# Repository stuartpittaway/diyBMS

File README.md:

# diyBMS
Do it yourself battery management system to Lithium ion battery packs/cells

More discussion
https://community.openenergymonitor.org/t/diy-lithium-battery-balancer-and-monitoring-bms/5594/10

** PLEASE NOTE THIS DESIGN HAS BEEN REPLACED WITH VERSION 4 **

https://github.com/stuartpittaway/diyBMSv4

# YouTube

https://www.youtube.com/watch?v=-CusvENqC4I&t=12s

Some Youtube videos on the BMS building and testing can be found at
https://www.youtube.com/playlist?list=PLiYbY8lzAN-2qB9rR0Sc7Z7sUrsgYzsiV

# Problem

A DIY Powerwall is the DIY construction of a pack of battery cells to create an energy store which can be used via inverters to power electrical items in the home. Generally cells are salvaged/second hand, and typically use Lithium 18650 cells.

Lithium batteries need to be kept at the same voltage level across a parallel pack. This is done by balancing each cell in the pack to raise or lower its voltage to match the others.

Existing balancing solutions are available in the market place, but at a relatively high cost compared to the cost of the battery bank, so this project is to design a low-cost, simple featured BMS/balancer.

A large number of people have utilised the commercial BATRIUM BMS system in their powerwall devices.

# My Situtation/Environment

UK based, but with only a small setup.  I have a 7s96p setup which i need to keep in balance.

# Existing Energy Usage

Through the monitoring of my home electric usage using the emonTX and emonSD solutions I typically use around 9kW/H per day (excluding electric car charging). Apart from odd spikes, load it generally less than 500W for the majority of the day/night.

# The Plan

Install a DIY powerwall with the ability to supply a 1000W load to cover all regular home usage (excluding spikes which the grid will handle).

A grid tied inverter would be required to convert the battery DC into mains level AC.

A controllable charger would be required to charge the battery during the day (or at cheap energy times from the grid). Ideally the charger should be able to match the generation of export from the solar array(s) to prevent import.

It may be possible to combine both charger and inverter into a single unit (so called hybrid units)

For obvious reasons, safety is critical, so care must be taken to ensure components are installed and certified as needed, along with the correct specification for cables, breakers and fuses etc.

Why am I doing this? For fun :slight_smile: I really must get out more!

# WARNING

Just a reminder that this is a DIY product/solution so don’t use this for safety critical systems or in any situation where there could be a risk to life.  There is no warranty, it may not work as expected or at all.

# Parameters

I’m working to the the following design parameters, which are taken from research into the area (what most others are doing!)

Assumption that second hand 18650 cells are made into “packs” containing tens or hundreds of cells in parallel.
Voltage of 18650 cell between 3.0V (empty) and 4.2V (full)
48V DC battery pack - running 14 packs/cells in series (aka 14S) this gives between 42V and 58.8V DC
Battery expected to output (1000W) so produce up to 25A current (depending on battery voltage)
Charger and inverter would be commercial products (not DIY) to comply with necessary approvals

# BMS Design

Building upon my existing skill set and knowledge, and also building something that others can contribute to using regular standard libraries and off the shelf components.

* Design a hub and spoke arrangement, for a central controller and individual cell monitoring nodes on each pack (so 14 in my case)
* Use Arduino based libraries and tools (possible move to platform.io) **
* Use esp8266-12e as the controller - to take advantage of built in WIFI for monitoring/alerting and CPU/RAM performance
* Use AVR ATTINY85 for each node
* Ensure each cell voltage is isolated from other cells and that ground voltage is isolated
* Isolated communications between controller and node is needed
* Put everything on GITHUB
* Document it!

** There are better more capable CPUs than the 8-bit Arduino however they lack user friendliness and the community to support and nuture the development of code

# Bill Of Materials

NOTE SIZES OF COMPNENTS SHOULD BE 0805 SIZED FOR THE SMALLER PCB VARIANT!

See BMS_Cell_Module_BOM.html for details

Links to main components
ATTINY85V-10SU
http://uk.farnell.com/atmel/attiny85v-10su/mcu-8bit-attiny-10mhz-soic-8/dp/1455166

REG710NA-3.3
http://uk.farnell.com/texas-instruments/reg710na-3-3-250/charge-pump-regulator-buck-boost/dp/1535743

Analog Devices ADUM1250ARZ
http://uk.farnell.com/analog-devices/adum1250arz-rl7/digital-isolator-4-ch-1mbps-nsoic/dp/2758723

SI2312BDS-T1-E3 MOSFET Transistor, N Channel, 3.9 A, 20 V, 0.025 ohm, 4.5 V, 850 mV
http://uk.farnell.com/vishay/si2312bds-t1-e3/mosfet-n-ch-20v-3-9a-sot-23-3/dp/2396085

B57891M0103K000 Thermistor, NTC, 10 kohm, B57891M Series, 3950 K, Through Hole
http://uk.farnell.com/epcos/b57891m0103k000/thermistor-ntc-radial-leaded/dp/2285471?ost=B57891M0103K000&iscrfnonsku=false&ddkey=http%3Aen-GB%2FElement14_United_Kingdom%2Fsearch

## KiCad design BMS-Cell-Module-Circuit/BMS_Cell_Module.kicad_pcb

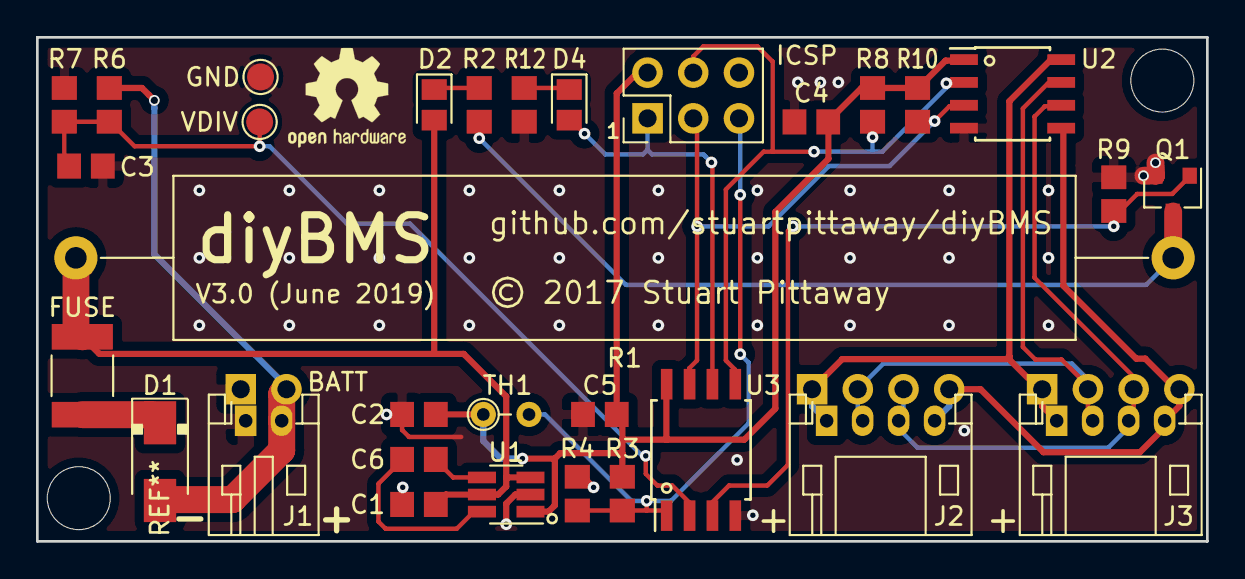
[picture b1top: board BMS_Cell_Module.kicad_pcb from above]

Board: 2 copper layers, 65.0 x 28.0 mm, 31 parts (0 on the bottom side), 20 nets.

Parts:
C1, C2: 2.2uF; C_0805_2012Metric_Pad1.33x1.40mm_HandSolder
C3, C4, C5: 0.1uF; C_0805_2012Metric_Pad1.33x1.40mm_HandSolder
C6: 0.22uF; C_0805_2012Metric_Pad1.33x1.40mm_HandSolder
D1: SS34 Schottky 40V/3A; DO-221AC
D2: LED BLUE; LED_0805_2012Metric_Pad1.15x1.40mm_HandSolder
D4: LED GREEN; LED_0805_2012Metric_Pad1.15x1.40mm_HandSolder
F1: FUSE; R_1812_4532Metric_Pad1.42x3.40mm_HandSolder
ISP1: Conn_02x03_Odd_Even; Pin_Header_Straight_2x03_Pitch2.54mm
J1: Conn_01x02_Female; JST_PH_S2B-PH-K_02x2.00mm_Angled
J2, J3: Conn_01x04_Female; JST_PH_S4B-PH-K_04x2.00mm_Angled
Q1: SI2312BDS-T1-E3; SOT-23
R1: 2R/10W; R_Axial_Power_L50.0mm_W9.0mm_P60.96mm
R2, R8, R10, R12: 4K7; R_0805_2012Metric_Pad1.33x1.40mm_HandSolder
R3: 20K; R_0805_2012Metric_Pad1.33x1.40mm_HandSolder
R4: 10K; R_0805_2012Metric_Pad1.33x1.40mm_HandSolder
R6: 510K; R_0805_2012Metric_Pad1.33x1.40mm_HandSolder
R7: 680K; R_0805_2012Metric_Pad1.33x1.40mm_HandSolder
R9: 47K; R_0805_2012Metric_Pad1.33x1.40mm_HandSolder
TH1: B57891M0103K000; R_Axial_DIN0204_L3.6mm_D1.6mm_P2.54mm_Vertical
TP1: VDIV; TestPoint_Pad_D1.5mm
TP2: TPGND; TestPoint_Pad_D1.5mm
U1: REG710NA-3.3; SOT-23-6_Handsoldering
U2: ADUM1250ARZ; SOIC-8_3.9x4.9mm_P1.27mm
U3: ATTINY85V-10SU 8S2 EIAJ SOIC; SOIJ-8_5.3x5.3mm_P1.27mm

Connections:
3V3: C2.1, C4.1, C5.1, ISP1.2, R3.1, R8.2, R10.2, TH1.1, U1.1, U2.1, U3.8
/MISO: D4.2, ISP1.1, U3.6
/MOSI: ISP1.4, R8.1, U2.2, U3.5
/PB4BYPASS: Q1.1, R9.1, U3.3
/RST: ISP1.5, R3.2, R4.1, TH1.2, U3.1
/SCK: ISP1.3, R10.1, U2.3, U3.7
BATT+RAW: D1.2, J1.2, R6.1
GND: C1.2, C2.2, C3.2, C4.2, C5.2, ISP1.6, J1.1, Q1.2, R4.2, R7.2, R9.2, R12.2, TP2.1, U1.2, U2.4, U3.4
unnamed: C1.1, D2.2, F1.1, R1.2, U1.3, U1.5
unnamed: C3.1, R6.2, R7.1, TP1.1, U3.2
unnamed: C6.1, U1.6
unnamed: C6.2, U1.4
unnamed: D1.1, F1.2
unnamed: D2.1, R2.2
unnamed: D4.1, R12.1
unnamed: J2.1, J3.1, U2.8
unnamed: J2.2, J3.2, U2.7
unnamed: J2.3, J3.3, U2.6
unnamed: J2.4, J3.4, U2.5
unnamed: Q1.3, R1.1, R2.1

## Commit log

2017-11-09 Initial cell monitoring circuit
2017-11-09 Started work on PCB
    DONT USE THIS PCB FOR PRODUCTION!
2017-11-12 Split board into two sections
2017-11-13 Split PCB into two halves
2017-11-13 All pins connected on PCB
2017-11-13 PCB files
2017-11-14 Update fuse and power socket
2017-11-14 Added ground plane to pcb
2017-11-14 First Gerber files
2017-11-14 Remove obsolete files
2017-11-14 Remove files
2017-11-16 Updated gerbers with bottom solder mask
2017-11-16 Project file changes
2017-11-17 Beta code in development
2017-11-17 Added header text
2017-11-18 Getting i2c to work properly
2017-11-19 Debugging ESP8266 crappy i2c issues
    Clock stretching appears to be breaking ESP8266 code
2017-11-20 Working i2c using wire library
2017-11-20 Changed freq to 8Mhz to improve i2c handling
2017-11-20 Delay after changing MUX in ADC ISR
2017-11-22 Write configuration to EEPROM and trigger LED on TIMER1
2017-11-22 Code tidy
2017-11-23 Implemented watchdog timeout and factory reset functions
2017-11-23 Commands to retrieve calibration values
2017-11-25 Added set calibration values functions
2017-11-26 Removed RED led and improved test functions in temporary controller
2017-11-26 Remove red led code
2017-11-27 Changed default values
2017-11-27 Test controller instructions and auto cell module provisioning
2017-11-27 Fixed error/panic mode
2017-11-27 Initial code for resistor bypass/balancing
2017-11-29 Started redesign of PCB
2017-12-02 Start of new PCB layout for v2
2017-12-02 Custom PCB footprints
2017-12-02 Updated PCB layout
2017-12-03 Revised PCB
2017-12-03 New Gerbers
2017-12-03 Update BOM
2017-12-03 Update pictures
2017-12-08 Remove backup files
2017-12-08 Tidy up test controller code
2017-12-08 Start of real DIY BMS controller
2017-12-10 Wifi AP configuration and setup
2017-12-11 Changed EEPROM update and write
2017-12-11 Split into seperate files
2017-12-11 Split code into seperate files
2017-12-11 Fixed CRC32 code not use the library!
2017-12-12 Post data into emoncms for cell module voltages and temperatures
2017-12-14 Submit Docs
2017-12-14 Set theme jekyll-theme-tactile
2017-12-14 HTML pages
2017-12-14 Added code to get IP address
2017-12-14 Graph to display
2018-01-06 Minor tweaks
2018-01-06 Testing javascript loading
2018-01-06 Test
2018-01-06 Test 2
2018-01-06 Changed async
2018-01-06 Swap to google loader
2018-01-06 More tinkering
2018-01-06 loader.js
2018-01-06 test 4
2018-01-06 Typo
2018-01-06 trigger('create');
2018-01-06 Load into body
2018-01-06 Draw graph
2018-01-06 alert
2018-01-06 Fix css
2018-01-06 loader
2018-01-06 console.log
2018-01-06 graph
2018-01-06 ajax
2018-01-06 Change url
2018-01-06 Style graph
2018-01-06 fix json
2018-01-06 Format 2nd axis
2018-01-06 Divide by 1000
2018-01-06 axes
2018-01-06 Missing {
2018-01-07 Improved graph
2018-01-08 Moved jquery commands
2018-01-08 Tidy html
2018-01-08 Missing bracket
2018-01-08 Refresh graph every 5s
2018-01-15 Store min/max voltage over time
2018-01-15 Updated code for provision button
2018-01-23 Enable cell provisioning and calibration functions
2018-01-25 Configuration of emonCMS now through web interface and stored in EEPROM
2018-01-25 Wrong link to part on Farnell
2018-02-04 Initial attempt at cell balancing
2018-02-04 Auto disable bypass when controller startsup
2018-02-04 Return target bypass value to web
2018-02-04 Change led pattern to light after comms and return correct voltage during bypass
2018-02-04 Fix flashing led issues
2018-02-06 Factory reset and resistance calibration
2018-02-06 Dynamic size graph height
2018-02-06 Web pages for new calibration options
2018-02-06 Configure resistance of bypass load
2018-02-07 Automatic temperature calibration sync
2018-02-07 Fix url
2018-02-07 Style sheet changes
2018-02-07 Added voltage calibration function
2018-03-15 Minor amends
2018-03-15 Updated Gerbers
2018-03-22 Remove obsolete call
2018-04-01 Set theme jekyll-theme-cayman
2018-04-01 grafana testing
2018-04-01 loader.js testing
2018-04-05 InfluxDB Integration
    Vast changes to add in influxdb support as well full configuration support the same as emonCMS
2018-04-06 js.loader
2018-04-07 Wire.setClockStretchLimit
    Change Wire.setClockStretchLimit(1500); and order.
2018-04-07 debugging
2018-04-08 check for invalid voltages.
2018-04-14 Update Bill Of Materials in README for readability.
    Grouped the capacitor and resistor values, ordering by their schematic name.
2018-04-22 Grafana post check
    Check for invalid values before posting to grafana now working.
2018-04-22 strech limit
    Strech limit set to 2000 which is now giving consitently reliable values.
2018-04-23 Temp+influxdb
    I've changed the structure of the influxdb to incorporate temp and bypass status per module. Temps are now converted to celcius as well.
2018-04-23 Graph Scale
    Updated the graph scale to a max of 100 now temps are converted to celsius.
2018-07-16 bypass-status addition
2018-07-16 avebalancecancel
2018-07-16 Readme
2018-07-16 Cancelling Balancing option
2018-07-17 graphing
2018-07-17 bypass-display
2018-07-17 bypass
2018-07-17 limit
2018-07-17 limit removal
2018-07-17 bypass posting emoncms
2018-07-17 bypass settings loader.js
2018-07-17 balance
2018-07-17 auto balancing
2018-07-17 autobalance
2018-07-17 auto balance
2018-07-17 form checking
2018-07-17 steps
2018-07-17 Change to 2 decimal places resolution
2018-07-19 Report balancing status to influxdb
2018-07-19 ResetESP option
2018-07-19 ESP-Reset-mod
2018-07-19 reset
2018-07-19 Tidy
2018-07-20 Balance to 2 decimal places
2018-07-22 Update R3 value in schematic to match pcb
    In #5 I had set R3 to 68K based on the schematic value, rather than the 20k value on the PCB. This fixes the discrepancy.
2018-08-13 Inverter Monitoring
    This allows the connection of an ACS712 to pin A0 which allows you to monitor the current draw of an external inverter.
2018-08-13 inverter monitor fix
2018-08-13 bugfix
2018-08-13 update save web interface
2018-08-13 Web interface order
2018-08-13 Inverter correction
2018-09-02 Updated KICAD to version 5 (no circuit changes)
2018-09-02 Fix for issue #12
2018-09-26 First check in
2018-09-26 resistor values to 4.7K instead of 2.2K
    Working version, simplified some resistor values to 4.7K instead of 2.2K to reduce number of resistor types needed
2018-09-27 Updated images
2018-09-27 Change BOM
2018-09-27 Removed URLs for incorrect sized compontents
2018-09-27 Update ignore file
2018-09-27 Remove backup file
2018-12-04 Change resistor value to prevent reset during cold temp conditions
    Fix issue #16
2018-12-04 Updated BOM
2019-02-27 Don't hide password to WIFI.
    This is only for you, very help solution. Will solve the problem with entering the password incorrectly.
2019-03-26 Minor amends and change SSID to indicate v3
2019-04-01 Update BMS_Cell_Module_BOM.html
    Added sizes to resistors and caps to avoid confusion and added links for components to vendor websites.
2019-05-30 added digikey bom for easy parts ordering
2019-06-25 Updated Gerber files after removal of R5
2019-06-25 Working Gerbers (June)

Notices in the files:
BMS-Cell-Module-Circuit/BMS_Cell_Module.kicad_pcb:
© 2017 Stuart Pittaway
© 2017-19 Stuart Pittaway
